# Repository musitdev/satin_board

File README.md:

# satin_board
Audio Satin board hardware and software

All Satin Board hardware are released under the terms of the Creative Commons Attribution-ShareAlike 4.0 International License, available here: http://creativecommons.org/licenses/by-sa/4.0/.
Satin board code is licenced has follow:
 * Firmware and SDK: Apache / MIT
 * applications: GPL 3.0

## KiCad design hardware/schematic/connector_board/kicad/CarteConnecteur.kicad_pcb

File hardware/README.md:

# satin_board
Audio Satin board hardware
Contains schematic, bom, kicad files and gerbers

Released under the terms of the Creative Commons Attribution-ShareAlike 4.0 International License, available here: http://creativecommons.org/licenses/by-sa/4.0/.

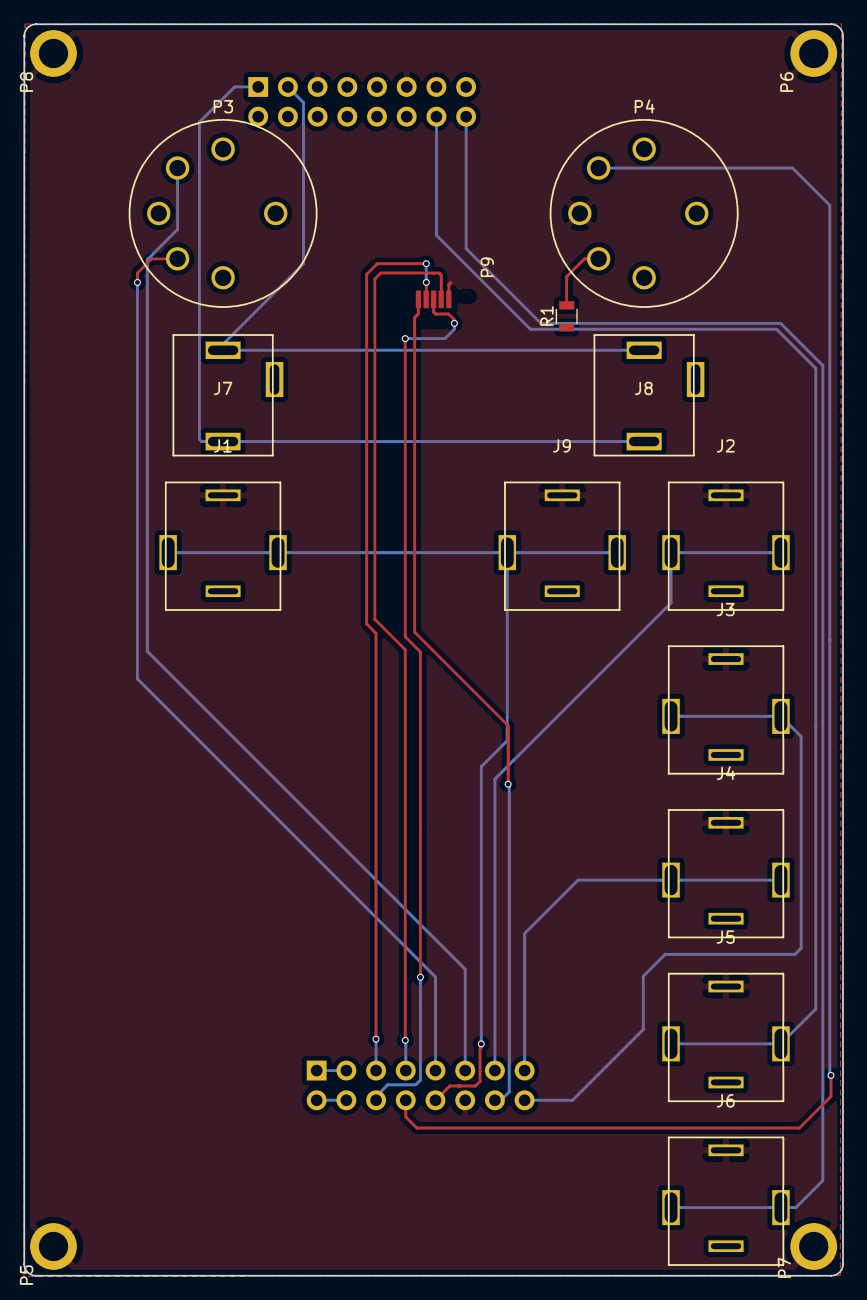
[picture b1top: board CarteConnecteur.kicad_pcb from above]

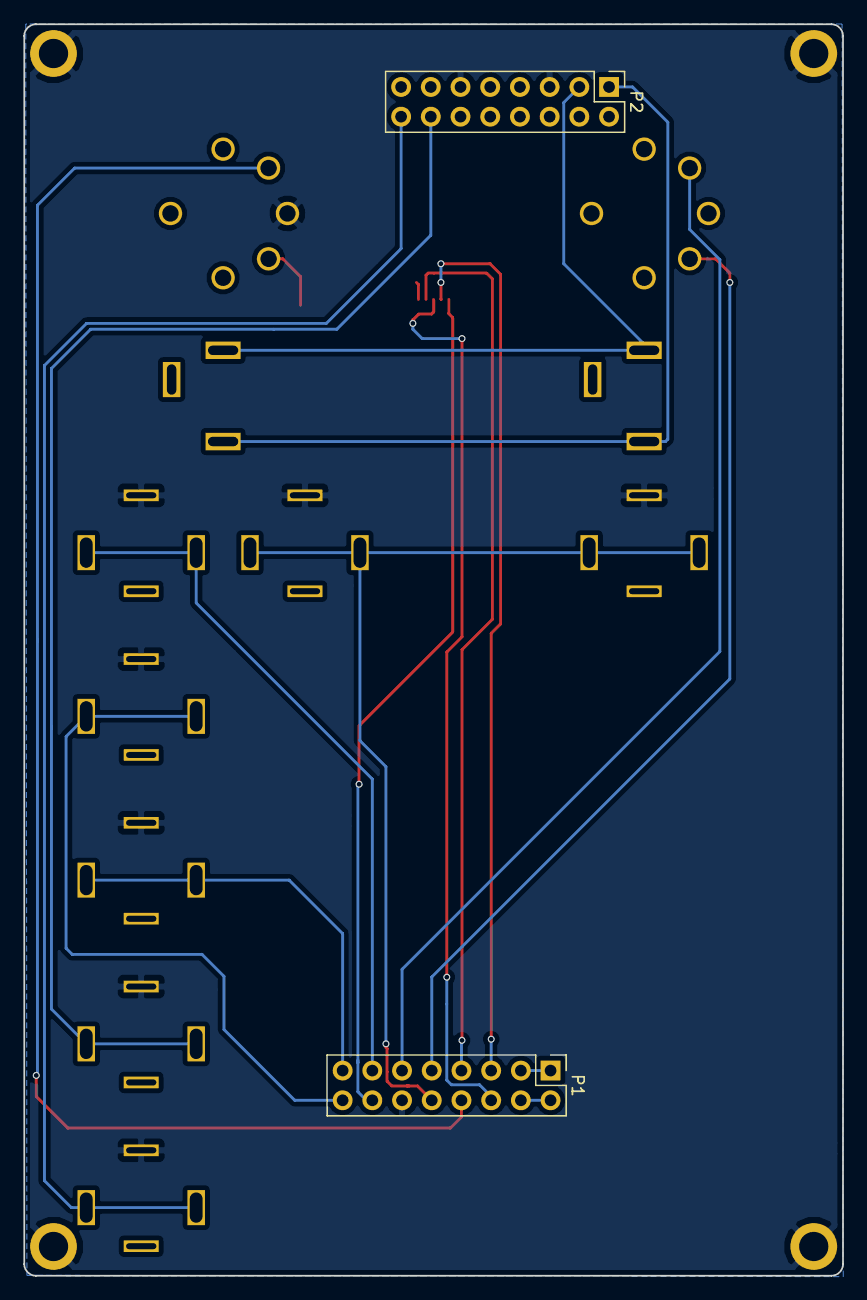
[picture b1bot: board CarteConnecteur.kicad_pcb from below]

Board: 2 copper layers, 70.0 x 107.0 mm, 19 parts (2 on the bottom side), 19 nets.

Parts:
J1, J2, J3, J4, J5, J6, J9: JACK_mono; PJ-301B
J7, J8: JACK_stereo; PJ301CM
P1, P2: CONN_02X08; Pin_Header_Straight_2x08_Pitch2.54mm
P3, P4: DIN_5; SD-50BV
P5, P6, P7, P8: Hole; Hole_2.5mm
P9: USB_OTG; USB_Micro-B-verticale
R1: 51; R_0805

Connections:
CLOCK_OUTPUT: J2.1, P1.13
CV_NOTE_OUTPUT: J3.1, P1.16
CV_VELOCITE_OUTPUT: J4.1, P1.15
CV_n3_OUTPUT: J5.1, P2.14
CV_n4_OUTPUT: J6.1, P2.16
GATE_OUTPUT: J1.1, J9.1, P1.10
GND: J1.3, J2.3, J3.3, J4.3, J5.3, J6.3, J9.3, P1.12, P2.5, P2.11, P4.2, P5.1, P6.1, P7.1, P8.1, P9.5
MIDI_INPUT+: P1.9, P3.4
MIDI_INPUT-: P1.11, P3.5
MIDI_OUTPUT: P1.8, P4.5
unnamed: P1.2, P1.4
unnamed: P4.4, R1.2
OUT_STEREO_LEFT: J7.3, J8.3, P2.1
OUT_STEREO_RIGHT: J7.2, J8.2, P2.3
PA10_USB_ID: P1.7, P9.4
USB_DM: P1.5, P9.2
USB_DP: P1.6, P9.3
VPP: P1.1, P1.3
VUSB_5V: P1.14, P9.1

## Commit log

2019-02-10 update with recent crate version
2019-02-10 remove old firmware
2019-02-10 new firmware
2019-02-10 add stm32f7 Hal
2019-02-10 update to compile mpecv
2019-02-14 add dad init
2019-02-14 update hal
2019-02-22 update connector board for PCB print, update Dac
2019-04-24 dac init and start SPI dac
2019-04-27 update RTFM
2019-04-28 add CV out managment
2019-04-28 do some test
2019-04-29 end Oxidize dev
2019-06-05 add some tests
2019-07-22 update new hal
2020-01-07 update with new dmq hal
2020-01-07 update cargo to build
2020-02-18 update for RTFMv5
2020-02-19 remove modified stm32f7xx-hal
2020-03-04 move serial management in satin board
